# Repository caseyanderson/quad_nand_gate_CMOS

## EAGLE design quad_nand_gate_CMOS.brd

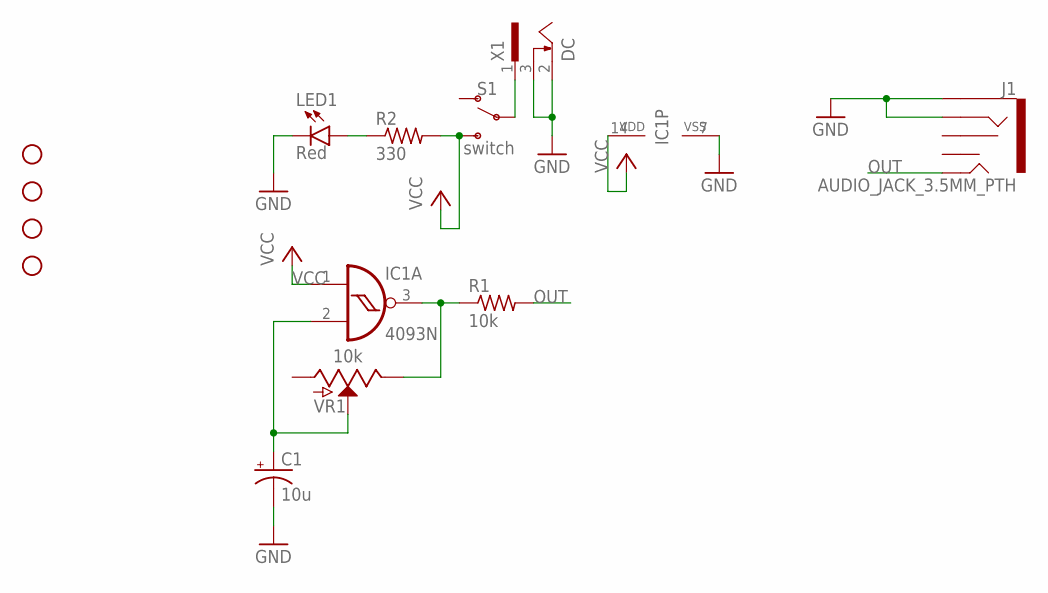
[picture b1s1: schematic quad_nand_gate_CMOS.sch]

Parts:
C1: 10u; E2,5-5
H1, H2, H3, H4: STAND-OFF
IC1: 4093N; DIL14
J1: AUDIO_JACK_3.5MM_PTH; AUDIO-JACK
LED1: Red; LED5MM
R1: 10k; 0204/5_66PADS
R2: 330; 0204/5_66PADS
S1: switch; SWITCH_SPDT_PTH_11.6X4.0MM_LOCK
VR1: 10k; POT-PTH-ALPS
X1: DC; SCD-014-A

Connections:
GND: C1.-, IC1.7 (VSS), J1.RING, J1.SLEEVE, LED1.K (C), X1.2, X1.3
unnamed: C1.+, IC1.2 (I1), VR1.P$2 (S)
unnamed: IC1.3 (O), R1.1, VR1.P$1 (E)
unnamed: S1.2, X1.1
unnamed: LED1.A, R2.1
OUT: J1.TIP, R1.2
VCC: IC1.1 (I0), IC1.14 (VDD), R2.2, S1.3 (S)

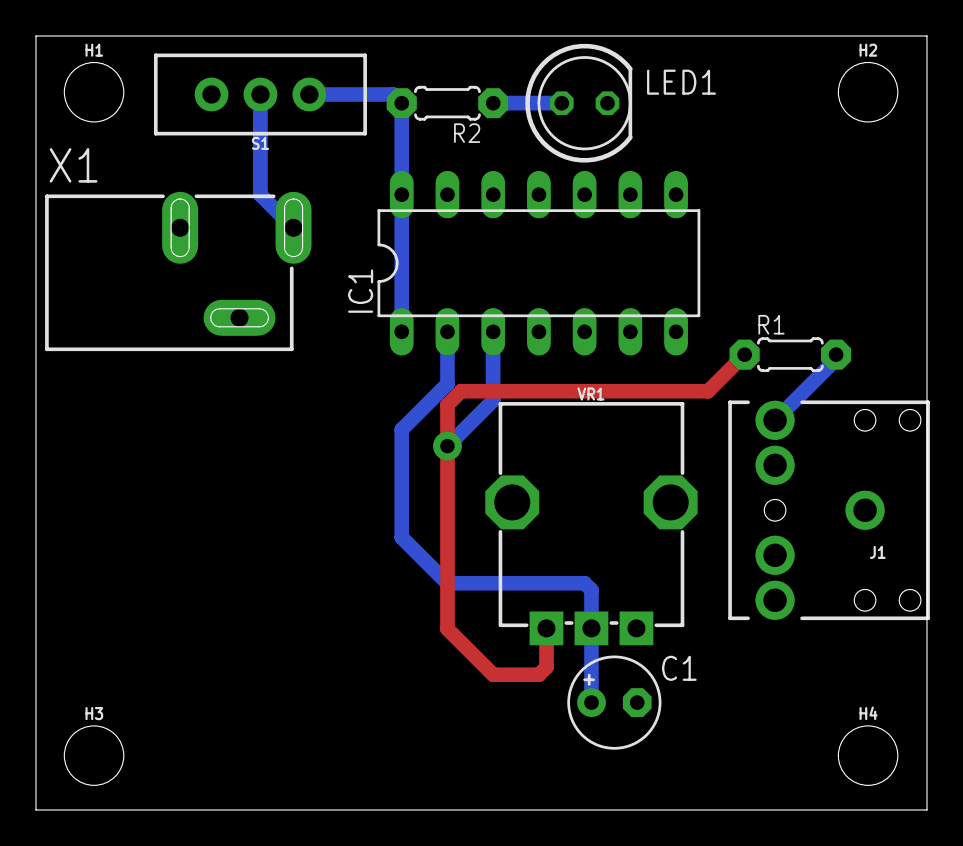
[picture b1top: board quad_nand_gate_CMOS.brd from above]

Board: 2 copper layers, 49.5 x 43.0 mm, 13 parts (0 on the bottom side), 7 nets.

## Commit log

2020-02-07 single osc quad nand gate repo exists now

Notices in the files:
parts and their libraries:
SparkFun-Connectors: Licensing: Creative Commons ShareAlike 4.0 International - https://creativecommons.org/licenses/by-sa/4.0
